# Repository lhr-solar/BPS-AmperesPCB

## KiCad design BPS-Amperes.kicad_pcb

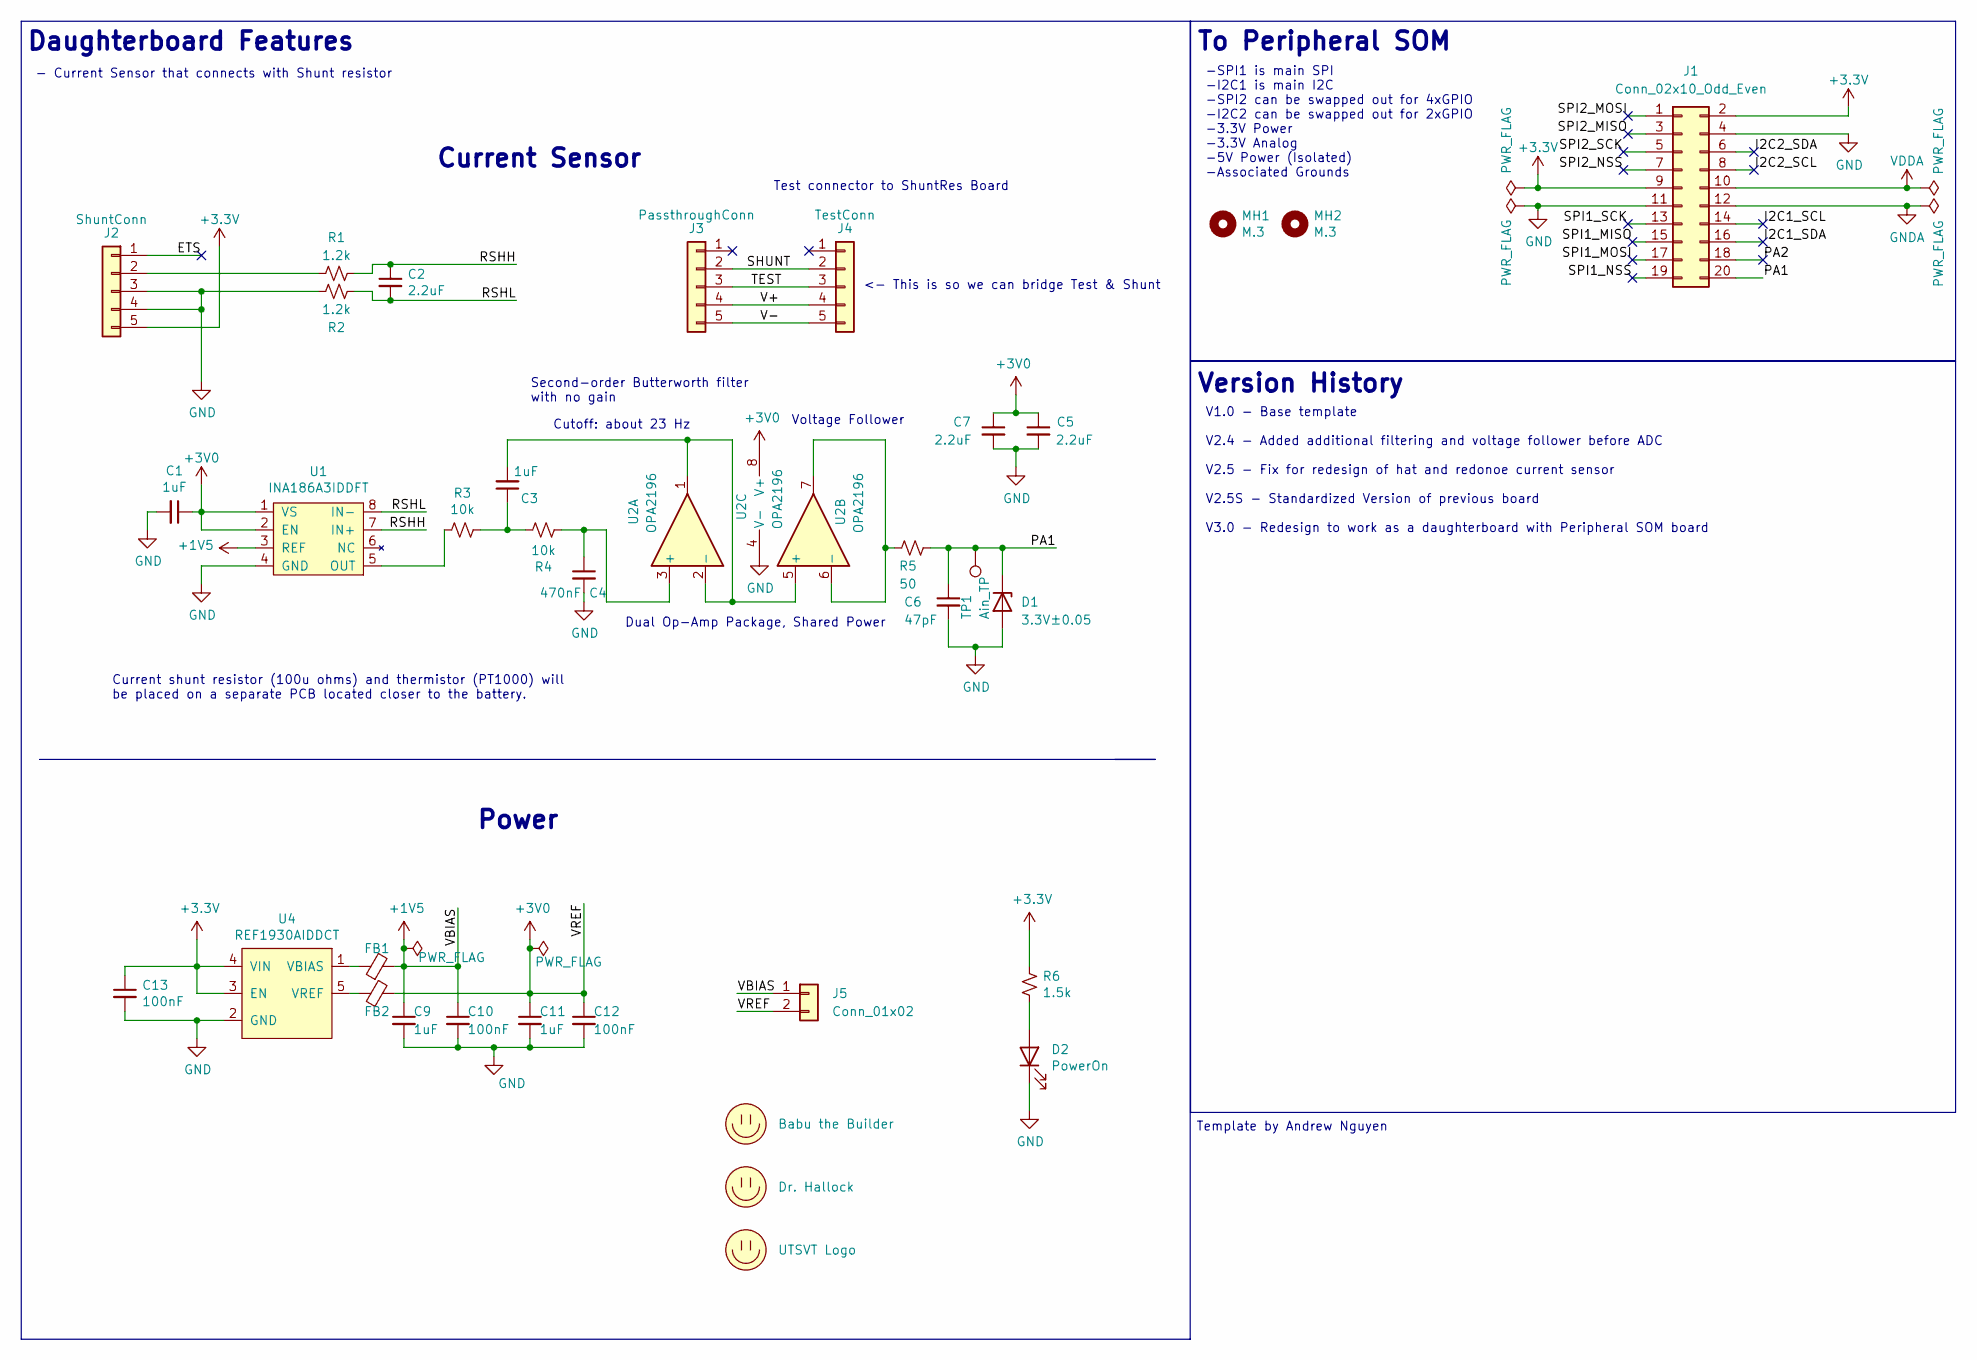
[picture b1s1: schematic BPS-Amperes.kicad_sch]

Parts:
C1, C3, C9, C11: 1uF; C_0805_2012Metric
C2, C5, C7: 2.2uF; C_0805_2012Metric
C4: 470nF; C_0805_2012Metric
C6: 47pF; C_0805_2012Metric
C10, C12, C13: 100nF; C_0805_2012Metric
D1: 3.3V±0.05; D_0805_2012Metric
D2: PowerOn; LED_0805_2012Metric
FB1, FB2: FerriteBead_Small; L_0805_2012Metric
J1: Conn_02x10_Odd_Even; Molex_53307-2071
J2: ShuntConn; PinSocket_1x05_P2.54mm_Vertical
J3: PassthroughConn; PinSocket_1x05_P2.54mm_Vertical
J4: TestConn; PinHeader_1x05_P2.54mm_Horizontal
J5: Conn_01x02; PinHeader_1x02_P2.54mm_Horizontal
LOGO0: Dr. Hallock; Hallock_Image_Tiny
LOGO1: UTSVT Logo; UTSVT_Logo_Symbol
LOGO2: Babu the Builder
MH1, MH2: M.3; MountingHole_3mm
R1, R2: 1.2k; R_0805_2012Metric
R3, R4: 10k; R_0805_2012Metric
R5: 50; R_0805_2012Metric
R6: 1.5k; R_0805_2012Metric
TP1: Ain_TP; PinHeader_1x01_P2.54mm_Horizontal
U1: INA186A3IDDFT; SOT-23-8
U2: OPA2196; SOIC-8_3.9x4.9mm_P1.27mm
U4: REF1930AIDDCT; SOT-23-5

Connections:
+1V5: C9.1, C10.1, FB1.2, J5.1, U1.3 (REF)
+3.3V: C13.1, J1.2, J1.9, J2.5, R6.1, U4.3 (EN), U4.4 (VIN)
+3V0: C1.1, C5.1, C7.1, C11.1, C12.1, FB2.2, J5.2, U1.1 (VS), U1.2 (EN), U2.8 (V+)
/ETS: J2.1
/I2C1_SCL: J1.14
/I2C1_SDA: J1.16
/I2C2_SCL: J1.8
/I2C2_SDA: J1.6
/PA1: C6.1, D1.1 (K), J1.20, R5.2, TP1.1
/PA2: J1.18
/RSHH: C2.1, R1.1, U1.7 (IN+)
/RSHL: C2.2, R2.1, U1.8 (IN-)
/SHUNT: J3.2, J4.2
/SPI1_MISO: J1.15
/SPI1_MOSI: J1.17
/SPI1_NSS: J1.19
/SPI1_SCK: J1.13
/SPI2_MISO: J1.3
/SPI2_MOSI: J1.1
/SPI2_NSS: J1.7
/SPI2_SCK: J1.5
/TEST: J3.3, J4.3
/V+: J3.4, J4.4
/V-: J3.5, J4.5
GND: C1.2, C4.2, C5.2, C6.2, C7.2, C9.2, C10.2, C11.2, C12.2, C13.2, D1.2 (A), D2.1 (K), J1.4, J1.11, J2.3, J2.4, R2.2, U1.4 (GND), U2.4 (V-), U4.2 (GND)
GNDA: J1.12
unnamed: C3.1, R3.1, R4.1
unnamed: D2.2 (A), R6.2
unnamed: J2.2, R1.2
unnamed: R3.2, U1.5 (OUT)
unnamed: C4.1, R4.2, U2.3 (+)
unnamed: C3.2, U2.1, U2.2 (-), U2.5 (+)
unnamed: R5.1, U2.6 (-), U2.7
unnamed: FB1.1, U4.1 (VBIAS)
unnamed: FB2.1, U4.5 (VREF)
VDDA: J1.10

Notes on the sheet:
To Peripheral SOM
Test connector to ShuntRes Board
Current shunt resistor (100u ohms) and thermistor (PT1000) will be placed on a separate PCB located closer to the battery.
- Current Sensor that connects with Shunt resistor
Current Sensor
Template by Andrew Nguyen
Dual Op-Amp Package, Shared Power
Second-order Butterworth filter with no gain
Voltage Follower
Power
Daughterboard Features
<- This is so we can bridge Test & Shunt
-SPI1 is main SPI -I2C1 is main I2C -SPI2 can be swapped out for 4xGPIO -I2C2 can be swapped out for 2xGPIO -3.3V Power -3.3V Analog -5V Power (Isolated) -Associated Grounds
V1.0 - Base template V2.4 - Added additional filtering and voltage follower before ADC V2.5 - Fix for redesign of hat and redonoe current sensor V2.5S - Standardized Version of previous board V3.0 - Redesign to work as a daughterboard with Peripheral SOM board
Version History
Cutoff: about 23 Hz

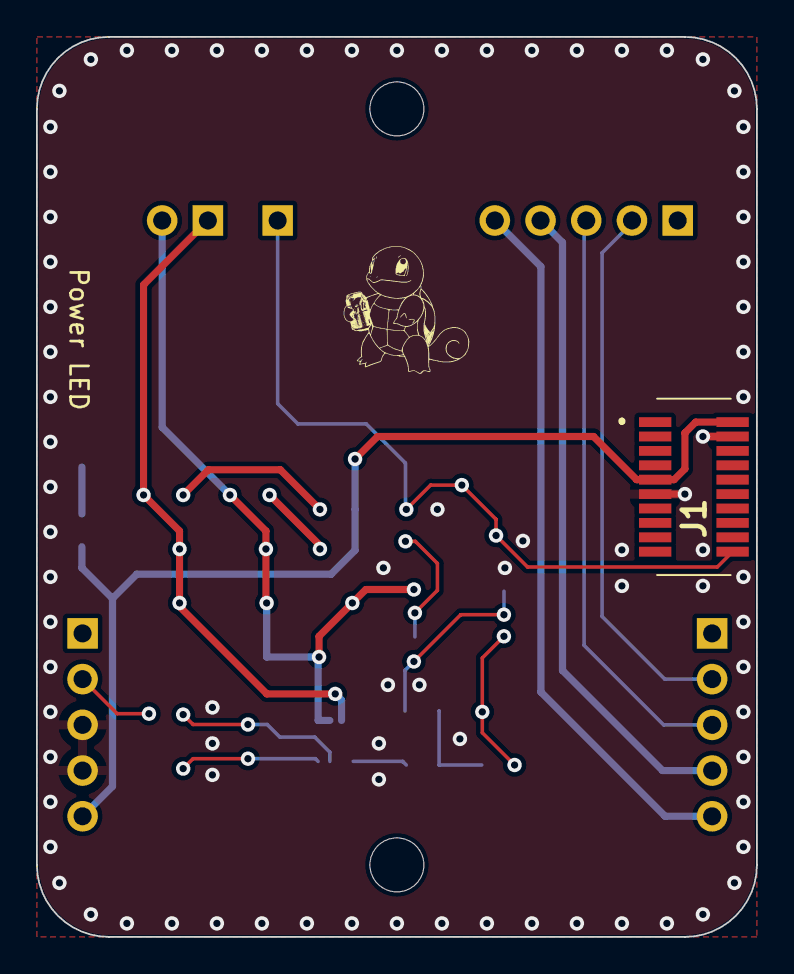
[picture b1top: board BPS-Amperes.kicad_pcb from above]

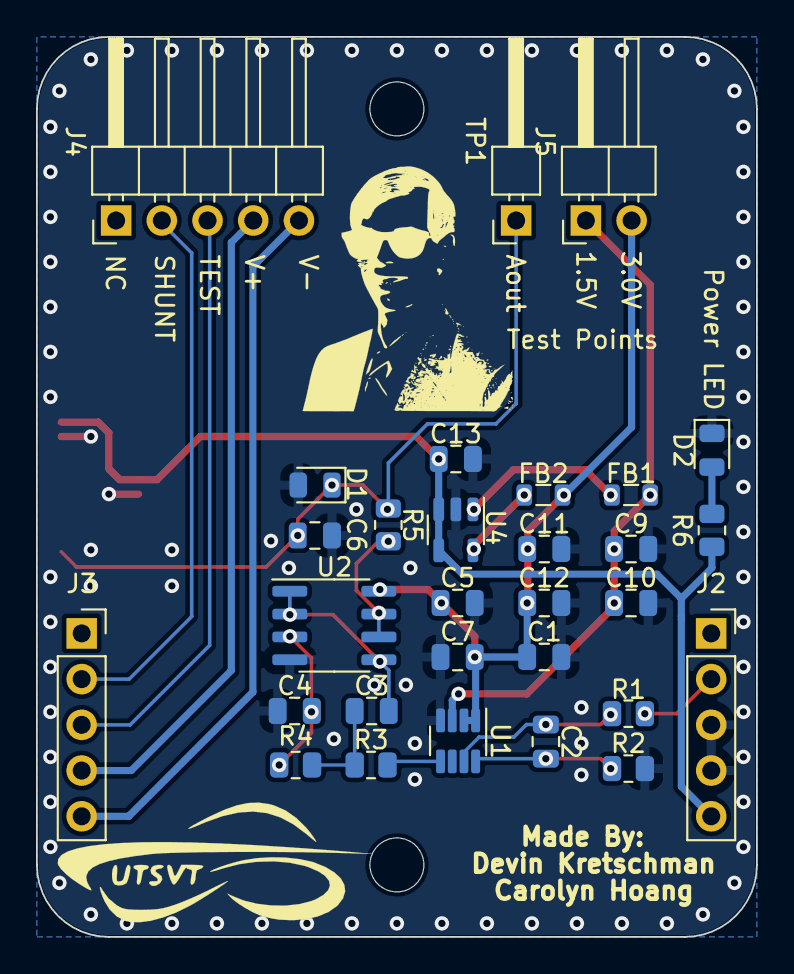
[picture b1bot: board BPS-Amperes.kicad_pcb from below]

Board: 2 copper layers, 40.0 x 50.0 mm, 35 parts (32 on the bottom side), 20 nets.

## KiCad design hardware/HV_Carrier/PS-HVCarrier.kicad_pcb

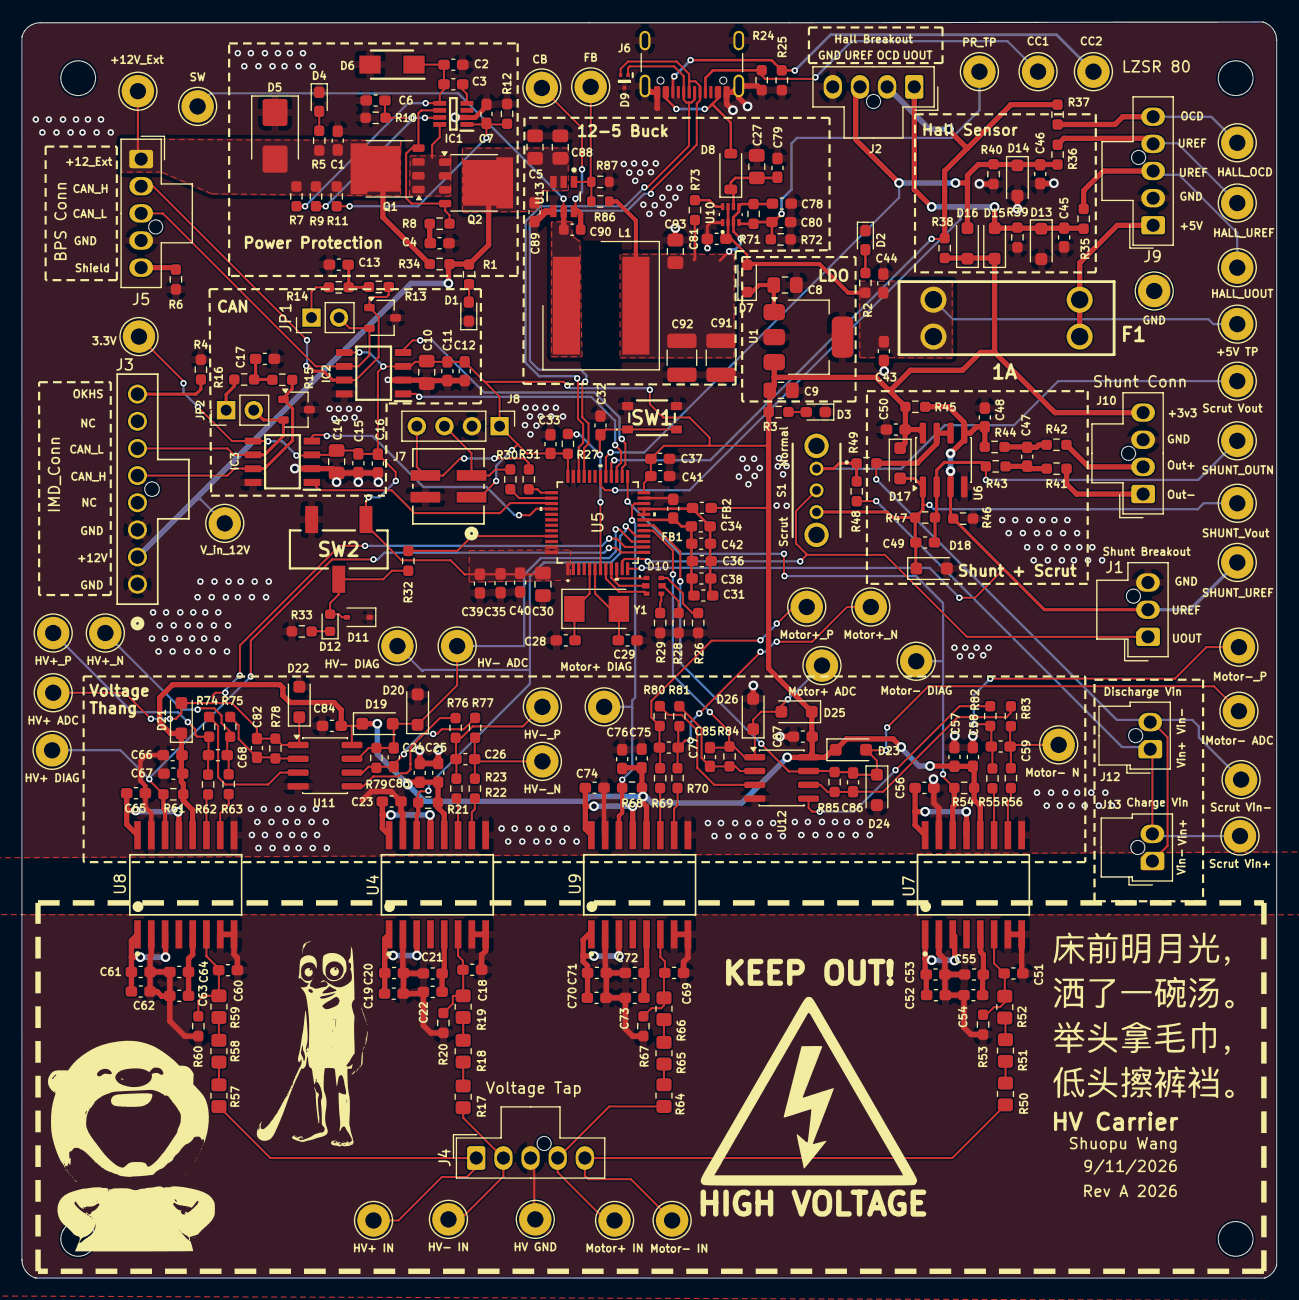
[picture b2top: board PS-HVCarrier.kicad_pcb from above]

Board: 2 copper layers, 115.6 x 115.7 mm, 291 parts (0 on the bottom side), 140 nets.

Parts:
C1, C6, C7, C11, C12, C13, C15, C16, C17, C50, C84, C87: 0.1u; C_0603_1608Metric_Pad1.08x0.95mm_HandSolder
C2, C25, C44, C58, C67, C76: 1u; C_0603_1608Metric_Pad1.08x0.95mm_HandSolder
C3: 220n; C_0603_1608Metric_Pad1.08x0.95mm_HandSolder
C4, C26, C45, C46, C59, C68, C77: 10n; C_0603_1608Metric_Pad1.08x0.95mm_HandSolder
C5, C8, C9, C10, C14, C27, C30: 10u; C_0805_2012Metric_Pad1.18x1.45mm_HandSolder
C18, C51, C60, C69: 100p; C_0603_1608Metric_Pad1.08x0.95mm_HandSolder
C19, C22, C24, C49, C52, C55, C57, C61, C64, C66, C70, C73, C75, C82, C83, C85, C86: 1n; C_0603_1608Metric_Pad1.08x0.95mm_HandSolder
C20, C21, C23, C42, C43, C47, C48, C53, C54, C56, C62, C63, C65, C71, C72, C74, C89: 100n; C_0603_1608Metric_Pad1.08x0.95mm_HandSolder
C28, C29: 26p; C_0603_1608Metric_Pad1.08x0.95mm_HandSolder
C31, C32, C33, C34, C35, C37, C39, C40, C41, C78, C79, C80, C81: 0.1uF; C_0603_1608Metric_Pad1.08x0.95mm_HandSolder
C36, C38: 1uF; C_0603_1608Metric_Pad1.08x0.95mm_HandSolder
C88: 4.7u; C_0805_2012Metric_Pad1.18x1.45mm_HandSolder
C90: 100n; C_0603_1608Metric
C91, C92: 22u; C_1210_3225Metric_Pad1.33x2.70mm_HandSolder
C93: 3.3u; C_0805_2012Metric_Pad1.18x1.45mm_HandSolder
D1, D2, D3, D4: LED; LED_0603_1608Metric_Pad1.05x0.95mm_HandSolder
D5: SMBJ15CA; D_SMB
D6: SMAF4758A; SODFL5026X125N
D7: SBA130CH-AU_R1_000A1; D_SOD-323_HandSoldering
D8: D_Schottky; D_SOD-123
D9: TPD2EUSB30DRTR
D10: RGB_LED
D11: TVS; D_SOD-323
D12: LED; LED_0603_1608Metric
D13, D14, D15, D16: D_SOD-123F
D17, D18, D19, D20, D21, D22, D23, D24, D25, D26: TVS; D_SOD-123F
F1: 1A; Fuse-3557-2
FB1, FB2: FerriteBead; C_0603_1608Metric_Pad1.08x0.95mm_HandSolder
H1, H2, H3, H4: MountingHole; MountingHole_3.2mm_M3
IC1: LM74502DDFR
IC2, IC3: TCAN3413DR
J1: Shunt Breakout; Molex_Nano-Fit_105309-xx03_1x03_P2.50mm_Vertical
J2: Hall Breakout; Molex_Nano-Fit_105309-xx04_1x04_P2.50mm_Vertical
J3: IMD_Conn; CONN_SD-105309-100_08_MOL
J4: Voltage Tap; Molex_Nano-Fit_105309-xx05_1x05_P2.50mm_Vertical
J5: BPS Conn; Molex_Nano-Fit_105309-xx05_1x05_P2.50mm_Vertical
J6: USB_C_Receptacle_USB2.0_16P; USB_C_Receptacle_GCT_USB4105-xx-A_16P_TopMnt_Horizontal
J7: SWD_Header; SWD_Conn
J8: SWD; PinHeader_1x04_P2.54mm_Vertical
J9: LZSR 80; Molex_Nano-Fit_105309-xx05_1x05_P2.50mm_Vertical
J10: Shunt Conn; Molex_Nano-Fit_105309-xx04_1x04_P2.50mm_Vertical
J12: Discharge Vin; Molex_Nano-Fit_105309-xx02_1x02_P2.50mm_Vertical
J13: Charge Vin; Molex_Nano-Fit_105309-xx02_1x02_P2.50mm_Vertical
JP1, JP2: TRM; PinHeader_1x02_P2.54mm_Vertical
L1: 8.2u; 74439369082
Q1, Q2: PSMN012-100YS; LFPAK56
R1, R5: 470; R_0603_1608Metric_Pad0.98x0.95mm_HandSolder
R2, R3: 150; R_0603_1608Metric_Pad0.98x0.95mm_HandSolder
R4: 2.1k; R_0603_1608Metric_Pad0.98x0.95mm_HandSolder
R6, R34: 0; R_0603_1608Metric_Pad0.98x0.95mm_HandSolder
R7, R27, R32, R35, R36, R37, R43, R44, R47, R49, R73, R74, R75, R76, R77, R78, R79, R80, R81, R82, R83, R84, R85: 10k; R_0603_1608Metric_Pad0.98x0.95mm_HandSolder
R8: 33; R_0603_1608Metric_Pad0.98x0.95mm_HandSolder
R9, R11: 100k; R_0603_1608Metric_Pad0.98x0.95mm_HandSolder
R10: 7.32k; R_0603_1608Metric_Pad0.98x0.95mm_HandSolder
R12: 15.8k; R_0603_1608Metric_Pad0.98x0.95mm_HandSolder
R13, R14, R15, R16: 60; R_0603_1608Metric_Pad0.98x0.95mm_HandSolder
R17, R18, R19, R50, R51, R52, R57, R58, R59, R64, R65, R66: 500k; R_0805_2012Metric_Pad1.20x1.40mm_HandSolder
R20, R38, R39, R40, R45, R46, R53, R60, R67: 20k; R_0603_1608Metric_Pad0.98x0.95mm_HandSolder
R21, R54, R61, R68: 47k; R_0603_1608Metric_Pad0.98x0.95mm_HandSolder
R22, R23, R55, R56, R62, R63, R69, R70: 10; R_0603_1608Metric_Pad0.98x0.95mm_HandSolder
R24, R25: 5.1k; R_0603_1608Metric_Pad0.98x0.95mm_HandSolder
R26, R28, R29, R33: 1k; R_0603_1608Metric_Pad0.98x0.95mm_HandSolder
R30, R31: 22; R_0603_1608Metric_Pad0.98x0.95mm_HandSolder
R41, R42: 100; R_0603_1608Metric_Pad0.98x0.95mm_HandSolder
R48: 90k; R_0603_1608Metric_Pad0.98x0.95mm_HandSolder
R71: 16k; R_0603_1608Metric_Pad0.98x0.95mm_HandSolder
R72: 4.7k; R_0603_1608Metric_Pad0.98x0.95mm_HandSolder
R86: 100k; R_0603_1608Metric
R87: 19.1k; R_0603_1608Metric
S1: OS102011MS2QN1; OS102011MA1QN1
SW1: Reset; TL3365AF180QG
SW2: SW_SPDT; BootSW
TP1: HV GND; TestPoint_THTPad_D3.0mm_Drill1.5mm
TP3: +5V TP; TestPoint_THTPad_D3.0mm_Drill1.5mm
TP4: GND; TestPoint_THTPad_D3.0mm_Drill1.5mm
TP5: +12V_Ext; TestPoint_THTPad_D3.0mm_Drill1.5mm
TP7: CC1; TestPoint_THTPad_D3.0mm_Drill1.5mm
TP8: CC2; TestPoint_THTPad_D3.0mm_Drill1.5mm
TP9: PR_TP; TestPoint_THTPad_D3.0mm_Drill1.5mm
TP10: HALL_UOUT; TestPoint_THTPad_D3.0mm_Drill1.5mm
TP11: HALL_UREF; TestPoint_THTPad_D3.0mm_Drill1.5mm
TP12: HALL_OCD; TestPoint_THTPad_D3.0mm_Drill1.5mm
TP13: SHUNT_OUTN; TestPoint_THTPad_D3.0mm_Drill1.5mm
TP14: SHUNT_UREF; TestPoint_THTPad_D3.0mm_Drill1.5mm
TP15: Scrut Vin+; TestPoint_THTPad_D3.0mm_Drill1.5mm
TP16: Scrut Vout; TestPoint_THTPad_D3.0mm_Drill1.5mm
TP17: Scrut Vin-; TestPoint_THTPad_D3.0mm_Drill1.5mm
TP18: SHUNT_Vout; TestPoint_THTPad_D3.0mm_Drill1.5mm
TP19: HV+ IN; TestPoint_THTPad_D3.0mm_Drill1.5mm
TP20: Motor+ IN; TestPoint_THTPad_D3.0mm_Drill1.5mm
TP21: HV+_P; TestPoint_THTPad_D3.0mm_Drill1.5mm
TP22: HV+_N; TestPoint_THTPad_D3.0mm_Drill1.5mm
TP23: Motor+_P; TestPoint_THTPad_D3.0mm_Drill1.5mm
TP24: Motor+_N; TestPoint_THTPad_D3.0mm_Drill1.5mm
TP25: HV+ DIAG; TestPoint_THTPad_D3.0mm_Drill1.5mm
TP26: Motor+ DIAG; TestPoint_THTPad_D3.0mm_Drill1.5mm
TP27: Motor- IN; TestPoint_THTPad_D3.0mm_Drill1.5mm
TP28: HV- IN; TestPoint_THTPad_D3.0mm_Drill1.5mm
TP29: HV-_P; TestPoint_THTPad_D3.0mm_Drill1.5mm
TP30: HV-_N; TestPoint_THTPad_D3.0mm_Drill1.5mm
TP31: Motor-_P; TestPoint_THTPad_D3.0mm_Drill1.5mm
TP32: Motor- N; TestPoint_THTPad_D3.0mm_Drill1.5mm
TP33: HV- DIAG; TestPoint_THTPad_D3.0mm_Drill1.5mm
TP34: Motor- DIAG; TestPoint_THTPad_D3.0mm_Drill1.5mm
TP35: HV- ADC; TestPoint_THTPad_D3.0mm_Drill1.5mm
TP36: HV+ ADC; TestPoint_THTPad_D3.0mm_Drill1.5mm
TP37: Motor+ ADC; TestPoint_THTPad_D3.0mm_Drill1.5mm
TP38: Motor- ADC; TestPoint_THTPad_D3.0mm_Drill1.5mm
TP39: V_in_12V; TestPoint_THTPad_D3.0mm_Drill1.5mm
TP40: CB; TestPoint_THTPad_D3.0mm_Drill1.5mm
TP41: FB; TestPoint_THTPad_D3.0mm_Drill1.5mm
TP42: SW; TestPoint_THTPad_D3.0mm_Drill1.5mm
TP_1: 3.3V; TestPoint_THTPad_D3.0mm_Drill1.5mm
U1: MCP1826S; SOT-223-3_TabPin2
U2, U3: CDSOT23-T24CAN
U4, U7, U8, U9: AMC3311QDWERQ1; DWE0016A-IPC_A
U5: STM32G473CETx; 48PinMCU
U6, U11, U12: TLV9002QDRQ1; SOIC-8_3.9x4.9mm_P1.27mm
U10: TPS2117DRLR
U13: LMR51635XDDCR; DDC0006A-MFG
Y1: Crystal; Crystal_SMD_Abracon_ABM3-2Pin_5.0x3.2mm

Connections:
/48PinMCU/BOOT0: R32.1, U5.45 (PB8-BOOT0)
/48PinMCU/GNDA: C31.2, C34.2, C36.2, C38.2, C42.2, FB1.1, U5.19 (VSSA)
/48PinMCU/NRST: C32.1, R27.1, SW1.1, U5.7 (PG10-NRST)
/48PinMCU/PA0: D10.5, U5.8 (PA0-GPIO_BLUE)
/48PinMCU/PA1: D10.3, U5.9 (PA1_GPIO_RED)
/48PinMCU/PA2: D10.1, U5.10 (PA2-GPIO_GREEN)
/48PinMCU/SWCLK: R30.1, U5.38 (PA14)
/48PinMCU/SWDIO: R31.1, U5.37 (PA13)
/48PinMCU/VDDA: C31.1, C34.1, C36.1, C38.1, C42.1, FB2.2, U5.20 (VREF+), U5.21 (VDDA)
/+3v3: C9.2, C10.1, C11.1, C12.1, C14.1, C15.1, C16.1, C24.1, C25.1, C30.1, C33.1, C35.1, C37.1, C39.1, C40.1, C41.1, C50.1, C57.1, C58.1, C66.1, C67.1, C75.1, C76.1, C84.1, C87.1, D15.1 (K), D16.1 (K), D17.1 (K), D19.1 (K), D21.1 (K), D23.1 (K), D25.1 (K), FB2.1, IC2.3 (VCC), IC2.5 (SHDNV_IO), IC3.3 (VCC), IC3.5 (SHDNV_IO), J7.1, J8.1, J10.4 (PWR), R3.1, R21.1, R27.2, R38.2, R45.2, R54.1, R61.1, R68.1, SW2.1 (A), TP_1.1 (1_1), U1.3 (VO), U4.12 (VDD), U5.1 (VBAT), U5.24 (VDD), U5.36 (VDD), U5.48 (VDD), U6.8 (V+), U7.12 (VDD), U8.12 (VDD), U9.12 (VDD), U11.8 (V+), U12.8 (V+)
/+5V: C43.1, C44.1, C81.1, D7.2 (A), F1.1, R2.1, TP3.1 (1_1), U10.2 (VOUT), U10.7 (VOUT__1)
/+12V: C5.1, C88.1, C89.1, J3.2, Q2.5, R1.1, R34.2, TP39.1 (1_1), U13.2 (EN), U13.3 (VIN)
/+12V_Ext: C1.1, D5.2 (A2), J5.1 (12V), Q1.5, R5.1, R7.2, R9.1, R11.1, R34.1, TP5.1 (1_1)
/BPS_CAN_H: IC2.7 (CANH), J5.2 (CAN_H), R13.1, U2.1 (CAN_H)
/BPS_CAN_L: IC2.6 (CANL), J5.3 (CAN_L), JP1.2 (B), U2.2 (CAN_L)
/CAN1_RX: IC3.4 (RXD), U5.40 (PB3)
/CAN1_TX: IC3.1 (TXD), U5.39 (PA15)
/CAN2_RX: IC2.4 (RXD), U5.26 (PB12)
/CAN2_TX: IC2.1 (TXD), U5.27 (PB13)
/Current_Sense/LZSR_OCD: J9.5 (OCD), R37.2, TP12.1 (1_1)
/Current_Sense/LZSR_UOUT: J9.3 (UOUT), R35.2, TP10.1 (1_1)
/Current_Sense/LZSR_UREF: J9.4 (UREF), R36.2, TP11.1 (1_1)
/Current_Sense/SHUNT Vout: C49.1, D17.2 (A), D18.1 (K), R47.1, S1.3, TP18.1 (1_1), U6.1
/Current_Sense/Scrut Vout: R48.2, R49.1, S1.1, TP16.1 (1_1)
/Current_Sense/Vin+: J12.1, J13.2, R48.1, TP15.1 (1_1)
/Current_Sense/Vin-: J12.2, J13.1, R49.2, TP17.1 (1_1), U6.6 (-), U6.7
/HALL_OCD: J2.2 (UREF), R37.1, R38.1, U5.28 (PB14)
/HALL_UOUT: C45.1, D13.1 (K), D15.2 (A), J2.1 (UOUT), R35.1, R39.2, U5.30 (PA8)
/HALL_UREF: C46.1, D14.1 (K), D16.2 (A), J2.3 (GND), R36.1, R40.2, U5.29 (PB15)
/HV+: J4.1 (HV+), R57.1, TP19.1 (1_1)
/HV+_ADC: C82.2, D21.2 (A), D22.1 (K), R78.1, TP36.1 (1_1), U5.14 (PA6), U11.1
/HV+_DIAG: R61.2, TP25.1 (1_1), U5.13 (PA5), U8.14 (DIAG)
/HV-: J4.2 (HV-), R17.1, TP28.1 (1_1)
/HV-_ADC: C83.2, D19.2 (A), D20.1 (K), R79.1, TP35.1 (1_1), U5.15 (PA7), U11.7
/HV-_DIAG: R21.2, TP33.1 (1_1), U4.14 (DIAG), U5.16 (PB0)
/IMD_CAN_H: IC3.7 (CANH), J3.5, R15.1, U3.1 (CAN_H)
/IMD_CAN_L: IC3.6 (CANL), J3.6, JP2.2 (B), U3.2 (CAN_L)
/IMD_OKHS: J3.8, R4.2
/MOTOR+_ADC: C85.2, D25.2 (A), D26.1 (K), R84.1, TP37.1 (1_1), U5.17 (PB1), U12.1
/MOTOR+_DIAG: R68.2, TP26.1 (1_1), U5.22 (PB10), U9.14 (DIAG)
/MOTOR-_ADC: C86.2, D23.2 (A), D24.1 (K), R85.1, TP38.1 (1_1), U5.18 (PB2), U12.7
/MOTOR-_DIAG: R54.2, TP34.1 (1_1), U5.25 (PB11), U7.14 (DIAG)
/Motor_Precharge+: J4.4 (MOTOR+), R64.1, TP20.1 (1_1)
/Motor_Precharge-: J4.5 (MOTOR-), R50.1, TP27.1 (1_1)
/Power_Data/12VBuck/CB: C90.1, TP40.1 (1_1), U13.6 (CB)
/Power_Data/12VBuck/FB: R86.2, R87.1, TP41.1 (1_1), U13.1 (FB)
/Power_Data/12VBuck/SW: C90.2, L1.1, TP42.1 (1_1), U13.5 (SW)
/Power_Data/Buck_5V: C78.1, C91.1, C92.1, C93.1, L1.2, R71.1, R73.1, R86.1, U10.3 (VIN1), U10.5 (MODE)
/Power_Data/PowerProtection/EN/UVLO: C7.2, IC1.1 (EN/UVLO), R11.2, R12.2
/Power_Data/PowerProtection/OV: C6.2, IC1.7 (OV), R9.2, R10.1
/Power_Data/PowerProtection/gate: IC1.6 (GATE), Q1.4, Q2.4, R8.2
/Power_Data/PowerProtection/source: IC1.8 (SRC), Q1.1, Q1.2, Q1.3, Q2.1, Q2.2, Q2.3
/Power_Data/Power_Mux/PR1: C80.1, R71.2, R72.1, TP9.1 (1_1), U10.4 (PR1)
/Power_Data/Power_Mux/VIN_2: C27.2, C79.1, D8.1 (K), U10.6 (VIN2)
/Power_Data/USB-C Connector/CC1: J6.A5 (CC1), R24.2, TP7.1 (1_1)
/Power_Data/USB-C Connector/CC2: J6.B5 (CC2), R25.2, TP8.1 (1_1)
/Power_Data/USB-C Connector/VBUS_IN: D8.2 (A), J6.A4 (VBUS), J6.A9 (VBUS), J6.B4 (VBUS), J6.B9 (VBUS)
/SHUNT_UOUT: J1.1 (UOUT), S1.2, U5.11 (PA3)
/SHUNT_UREF: C48.1, J1.2 (UREF), R44.1, R45.1, R46.1, TP14.1 (1_1), U5.12 (PA4), U6.3 (+), U6.5 (+)
/USB_D+: D9.1 (D+), J6.A6 (D+), J6.B6 (D+), U5.34 (PA12)
/USB_D-: D9.2 (D-), J6.A7 (D-), J6.B7 (D-), U5.33 (PA11)
/Voltage_Sense/HV+_N: C68.1, R63.2, R75.1, TP22.1 (1_1)
/Voltage_Sense/HV+_P: C68.2, R62.2, R74.1, TP21.1 (1_1)
/Voltage_Sense/HV-_N: C26.1, R23.2, R77.1, TP30.1 (1_1)
/Voltage_Sense/HV-_P: C26.2, R22.2, R76.1, TP29.1 (1_1)
/Voltage_Sense/Motor+_N: C77.1, R70.2, R81.1, TP24.1 (1_1)
/Voltage_Sense/Motor+_P: C77.2, R69.2, R80.1, TP23.1 (1_1)
/Voltage_Sense/Motor-_N: C59.1, R56.2, R83.1, TP32.1 (1_1)
/Voltage_Sense/Motor-_P: C59.2, R55.2, R82.1, TP31.1 (1_1)
GND: C1.2, C2.1, C4.2, C5.2, C6.1, C7.1, C8.1, C9.1, C10.2, C11.2, C12.2, C13.2, C14.2, C15.2, C16.2, C17.2, C23.2, C24.2, C25.2, C27.1, C28.1, C29.2, C30.2, C32.2, C33.2, C35.2, C37.2, C39.2, C40.2, C41.2, C43.2, C44.2, C45.2, C46.2, C48.2, C50.2, C56.2, C57.2, C58.2, C65.2, C66.2, C67.2, C74.2, C75.2, C76.2, C78.2, C79.2, C80.2, C81.2, C84.2, C87.2, C88.2, C89.2, C91.2, C92.2, C93.2, D1.1 (K), D2.1 (K), D3.1 (K), D4.1 (K), D5.1 (A1), D6.2 (A), D9.3 (GND), D11.1 (A1), D13.2 (A), D14.2 (A), D18.2 (A), D20.2 (A), D22.2 (A), D24.2 (A), D26.2 (A), FB1.2, IC1.2 (GND), IC2.2 (GND), IC2.8 (STB), IC3.2 (GND), IC3.8 (STB), J1.3 (GND), J2.4 (GND), J3.1, J3.3, J5.4 (GND), J6.A1 (GND), J6.A12 (GND), J6.B1 (GND), J6.B12 (GND), J6.S1 (SHIELD), J6.S2 (Shield), J6.S3 (Shield), J6.S4 (Shield), J7.2, J8.2, J9.2 (GND), J10.3 (GND), R4.1, R6.1, R10.2, R12.1, R24.1, R25.1, R26.2, R28.2, R29.2, R33.2, R39.1, R40.1, R46.2, R72.2, R87.2, SW1.2, SW2.3 (C), TP4.1 (1_1), U1.2 (GND), U2.3 (GND), U3.3 (GND), U4.9 (GND), U4.15 (DCDC_GND), U5.23 (VSS), U5.35 (VSS), U5.47 (VSS), U6.4 (V-), U7.9 (GND), U7.15 (DCDC_GND), U8.9 (GND), U8.15 (DCDC_GND), U9.9 (GND), U9.15 (DCDC_GND), U10.1 (GND), U11.4 (V-), U12.4 (V-), U13.4 (GND)
HV GND: C18.2, C19.2, C20.1, C21.1, C22.1, C51.2, C52.2, C53.1, C54.1, C55.1, C60.2, C61.2, C62.1, C63.1, C64.1, C69.2, C70.2, C71.1, C72.1, C73.1, J4.3 (GND), R20.1, R53.1, R60.1, R67.1, TP1.1 (1_1), U4.2 (DCDC_HGND), U4.7 (HGND), U4.8 (HGND), U7.2 (DCDC_HGND), U7.7 (HGND), U7.8 (HGND), U8.2 (DCDC_HGND), U8.7 (HGND), U8.8 (HGND), U9.2 (DCDC_HGND), U9.7 (HGND), U9.8 (HGND)
unnamed: C4.1, R8.1
unnamed: C13.1, R13.2, R14.1
unnamed: C17.1, R15.2, R16.1
unnamed: C47.1, R41.1, R43.2
unnamed: C47.2, R42.1, R44.2
unnamed: D1.2 (A), R1.2
unnamed: D2.2 (A), R2.2
unnamed: D3.2 (A), R3.2
unnamed: D4.2 (A), R5.2
unnamed: C2.2, C3.1, D6.1 (K), IC1.5 (VS), R7.1
unnamed: C8.2, D7.1 (K), U1.1 (VI)
unnamed: D10.2, R26.1
unnamed: D10.4, R28.1
unnamed: D10.6, R29.1
unnamed: D11.2 (A2), D12.2 (A), R32.2, SW2.2 (B)
unnamed: D12.1 (K), R33.1
unnamed: C3.2, IC1.4 (VCAP)
unnamed: J5.5 (SHIELD), R6.2
unnamed: J7.3, J8.3, R30.2
unnamed: J7.4, J8.4, R31.2
unnamed: F1.2, J9.1 (+UC)
unnamed: J10.2 (Out+), R42.2
unnamed: J10.1 (Out-), R41.2
unnamed: JP1.1 (A), R14.2
unnamed: JP2.1 (A), R16.2
unnamed: R17.2, R18.1
unnamed: R18.2, R19.1
unnamed: R50.2, R51.1
unnamed: R51.2, R52.1
unnamed: R57.2, R58.1
unnamed: R58.2, R59.1
unnamed: R64.2, R65.1
unnamed: R65.2, R66.1
unnamed: C23.1, U4.13 (LDO_OUT), U4.16 (DCDC_IN)
unnamed: C19.1, C20.2, U4.1 (DCDC_OUT), U4.3 (HLDO_IN)
unnamed: C21.2, C22.2, U4.5 (HLDO_OUT)
unnamed: C18.1, R19.2, R20.2, U4.6 (IN)
unnamed: R23.1, U4.10 (OUTN)
unnamed: R22.1, U4.11 (OUTP)
unnamed: C28.2, U5.5 (PF0-OSC_IN), Y1.1
unnamed: C29.1, U5.6 (PF1-OSC_OUT), Y1.2
unnamed: C49.2, R43.1, R47.2, TP13.1 (1_1), U6.2 (-)
unnamed: C56.1, U7.13 (LDO_OUT), U7.16 (DCDC_IN)
unnamed: C52.1, C53.2, U7.1 (DCDC_OUT), U7.3 (HLDO_IN)
unnamed: C54.2, C55.2, U7.5 (HLDO_OUT)
unnamed: C51.1, R52.2, R53.2, U7.6 (IN)
unnamed: R56.1, U7.10 (OUTN)
unnamed: R55.1, U7.11 (OUTP)
unnamed: C65.1, U8.13 (LDO_OUT), U8.16 (DCDC_IN)
unnamed: C61.1, C62.2, U8.1 (DCDC_OUT), U8.3 (HLDO_IN)
unnamed: C63.2, C64.2, U8.5 (HLDO_OUT)
unnamed: C60.1, R59.2, R60.2, U8.6 (IN)
unnamed: R63.1, U8.10 (OUTN)
unnamed: R62.1, U8.11 (OUTP)
unnamed: C74.1, U9.13 (LDO_OUT), U9.16 (DCDC_IN)
unnamed: C70.1, C71.2, U9.1 (DCDC_OUT), U9.3 (HLDO_IN)
unnamed: C72.2, C73.2, U9.5 (HLDO_OUT)
unnamed: C69.1, R66.2, R67.2, U9.6 (IN)
unnamed: R70.1, U9.10 (OUTN)
unnamed: R69.1, U9.11 (OUTP)
unnamed: R73.2, U10.8 (ST)
unnamed: R74.2, U11.3 (+)
unnamed: C82.1, R75.2, R78.2, U11.2 (-)
unnamed: R76.2, U11.5 (+)
unnamed: C83.1, R77.2, R79.2, U11.6 (-)
unnamed: R80.2, U12.3 (+)
unnamed: C85.1, R81.2, R84.2, U12.2 (-)
unnamed: R82.2, U12.5 (+)
unnamed: C86.1, R83.2, R85.2, U12.6 (-)

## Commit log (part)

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2021-10-30 Fixed connection to leader board
2022-09-17 update for newer kicad version
2022-09-24 emi, reverse polarity, and analog overvolt protection
2022-09-24 remove kicad 5.0 files
2022-09-24 ignore erc and add annotations
2022-10-01 more bypass caps and other fixes
2022-10-01 test pr submodule
2023-09-23 Initial commit importing Daughterboard template
2023-09-23 Copy paste schema and add labels
2023-09-30 Fixed submodule and added new Libraries branch
2023-09-30 Read Me update
2023-09-30 Added power flags
2023-09-30 Fixed misc warnings in ERC
2023-09-30 Final Schematic Changes, cleaned stuff up
2023-09-30 Added datasheet links
2023-09-30 Added Hallock and LHRs Logo
2023-09-30 Added LED
2023-09-30 Added BOM files
2023-09-30 Edited a MFG part number
2023-10-07 Rearranged power lines in schematic according to recommendations for cleaner look
2023-10-07 Updated terminating resistor orientation and location of bypass caps for ADC sampler
2023-10-07 Started Layout
2023-10-07 Added dims to readme
2023-10-07 Blocked out layout
2023-10-07 Blocked out some component layouts
2023-10-07 Blocked out component layout, (oops trying again)
2023-10-07 Initial Grouped Layout
2023-10-07 Moved components to back of PCB, currently rearranging
2023-10-07 Added Shunt Passthrough & Test Conns
2023-10-07 Added Mounting Holes to RShunt Board
2023-10-14 Layout updates
2023-10-14 Possible Main components orientation
2023-10-14 Sike we don't need mounting holes
2023-10-14 fix shunt conn positions
2023-10-14 Fix possible issue and revert
2023-10-14 Changed testpoints and arranged power components
2023-10-14 Initial Analog Circuit
2023-10-14 put analog smd items on top and layout stuffs
2023-10-14 Finished general placement of remaining components
2023-10-14 Finished general layout of remaining components
2023-10-21 Reworking first iteration v1
2023-10-21 fix broken layout
2023-10-21 Fixing spacing and reiterating on v1
2023-10-21 Rearranged power components
2023-10-21 Moved power components to the front and increased spacing between components
2023-10-21 Changed position of headers and labelled stuff
2023-10-21 Flipped components to the back
2023-10-21 adding ground plane to the back
2023-10-21 Initial tracing with no thoughts
2023-10-28 Updated component blocking
2023-10-28 Fixed 3.3V Zener & Read Me
2023-10-28 Fixed readme
2023-10-28 Manthan Suggestions
2023-10-28 Initial tracing, improvements to come via Tianda's review
2023-10-28 The Thickening
2023-11-04 adjusted traces
2023-11-04 Updated Mouser Bom, Added Stitching Vias
2023-11-04 Updated ReadMe to have LED Definition
2023-11-04 Added new logo
2023-11-08 Rearranged components and completed initial wiring to route on the front
2023-11-08 Fixed a couple of DRC errors missed in previous commit
2023-11-09 Added uniform outline vias
2023-11-09 Removed vias and flipped really short traces
2023-11-09 Added Analog protection stitching vias every ~6mm
2023-11-11 removed babu :pensive:
2023-11-11 Updated Gerbers and added Squirtle
2024-10-06 started the board and added the 226 and 293
2024-11-02 workday 1/4
2024-12-07 Corrections with resistor values and slight components
2025-01-18 1/18
2025-01-18 done
2025-01-25 New parts
2025-01-25 Testpoints and Math
2025-01-25 Daisy Chain CAN Connectors
